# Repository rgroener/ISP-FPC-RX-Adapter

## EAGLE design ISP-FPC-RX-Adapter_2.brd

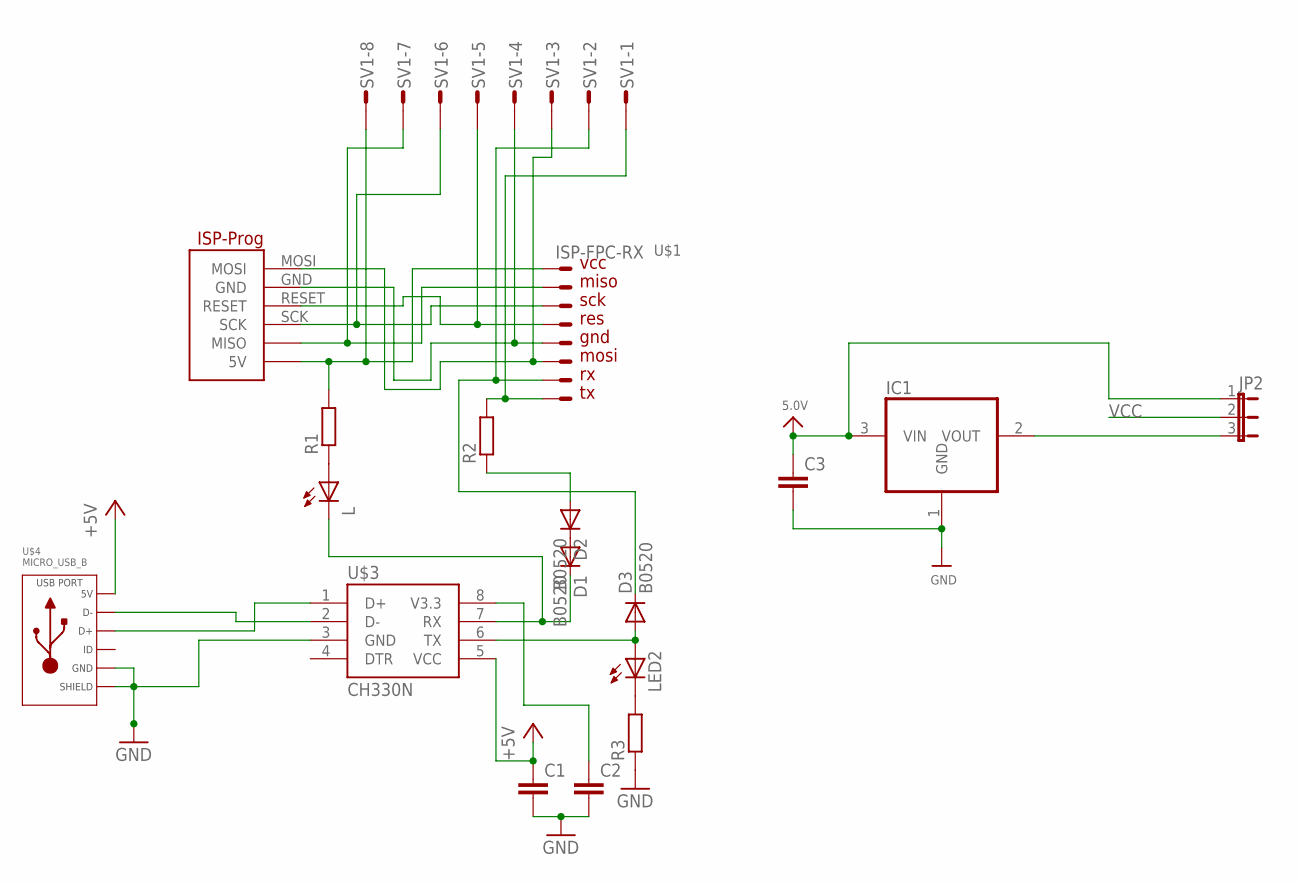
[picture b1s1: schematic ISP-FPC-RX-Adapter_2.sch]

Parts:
C1, C2: C-EUC0805; C0805
C3: C-EUC1206; C1206
D1, D2, D3: B0520; MELF-MLL41
IC1: SOT223
JP2: JP2E; JP2
L: LEDCHIP-LED0805; CHIP-LED0805
LED2: LEDCHIP-LED0805; CHIP-LED0805
R1, R2, R3: R-EU_R0805; R0805
SV1: S08P
U$1: ISP-FPC-RX
U$2: ISP_PROG_STECKERISP_PROG_WANNENSTECKER; ISP_PROG_WANNENSTECKER
U$3: CH330N; SOIC8
U$4: MICRO_USB_B

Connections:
5.0V: C3.1, IC1.3 (VIN), JP2.1
+5V: C1.1, U$3.5 (VCC), U$4.1 (5V)
DTR: U$3.4 (DTR)
GND: C1.2, C2.2, C3.2, IC1.1 (GND), R3.1, SV1.4, U$1.GND, U$2.GND, U$3.3 (GND), U$4.5 (GND), U$4.S1 (SLD), U$4.S2 (SLD), U$4.S5 (SLD), U$4.S6 (SLD), U$4.S7 (SLD), U$4.S8 (SLD)
MISO: SV1.7, U$1.MISO, U$2.MISO
MOSI: SV1.3, U$1.MOSI, U$2.MOSI
unnamed: U$3.2 (D-), U$4.2 (D-)
unnamed: U$3.1 (D+), U$4.3 (D+)
unnamed: D3.A, LED2.A, U$3.6 (TX)
unnamed: C2.1, U$3.8 (V3.3)
unnamed: IC1.2 (VOUT), JP2.3
unnamed: D1.C, L.C, U$3.7 (RX)
unnamed: L.A, R1.1
unnamed: D1.A, D2.C
unnamed: D2.A, R2.1
unnamed: LED2.C, R3.2
RES: SV1.5, U$1.RES, U$2.RESET
RX: D3.C, SV1.2, U$1.RX
SCK: SV1.6, U$1.SCK, U$2.SCK
TX: R2.2, SV1.1, U$1.TX
VCC: JP2.2, R1.2, SV1.8, U$1.VCC, U$2.5V

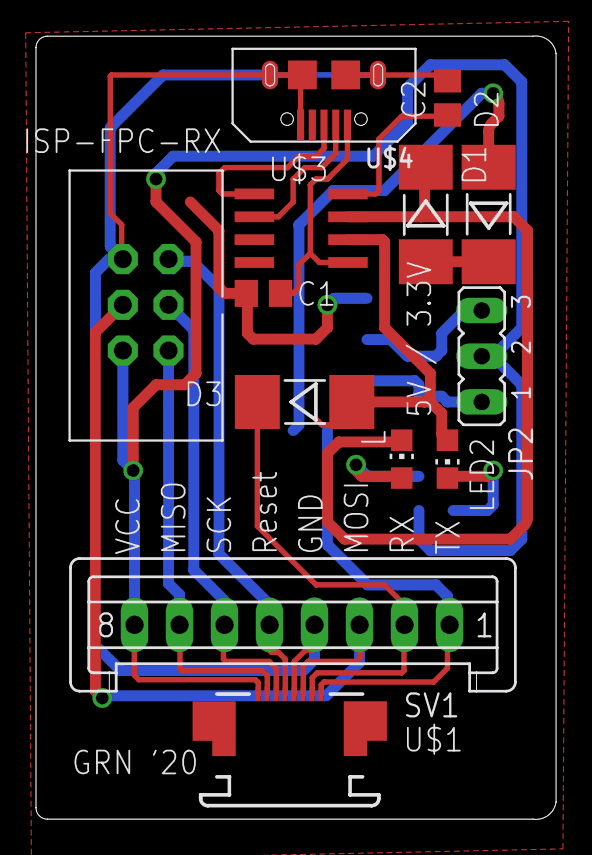
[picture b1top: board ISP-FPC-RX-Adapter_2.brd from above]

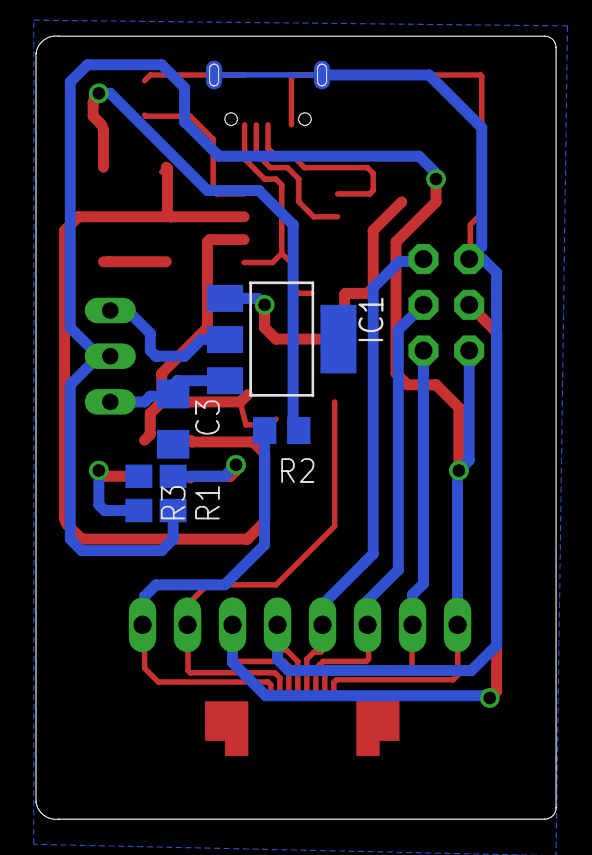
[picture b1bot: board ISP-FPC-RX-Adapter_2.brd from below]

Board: 2 copper layers, 28.9 x 43.5 mm, 18 parts (5 on the bottom side), 20 nets.

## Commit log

2020-11-17 added ordernr. LED Distrelec
2020-11-17 minor changes in bom.csv

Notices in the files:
parts and their libraries:
microbuilder: This work is placed in the public domain, and may be freely used for commercial and non-commercial work with the following conditions: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
